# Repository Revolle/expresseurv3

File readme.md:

#Expresseur project

documentation , presentation : www.expresseur.com

basslua This library can be used by a GUI, to manage MIDI inputs and LUA scripting (to invent your own MIDI logic). C library 64 bits. Started by the GUI, which load :

main lua script to catch the midi-event
luachord.lua
luascore.lua
luabass
dependencies :

lua5.3 64 bits : www.lua.org
bass 64 bits : www.un4see.com
winmm/pc, coremidi/Mac
luabass :

This library can be used to manage audio output (MIDI, VST, SF2, wav, DMX) from a LUA script. C library 64 bits. Started by lua script, to render midi-out, SF2, VSTi, Wav

dependencies :

lua5.3 64 bits : www.lua.org
bass, bassmix, bassmidi ( bassasio/PC ) 64 bits: www.un4seen.com
winmm/pc, coremidi/Mac
vsti sdk (include only, dynamic VSTi-dll loaded dynamically on demand)
expresscmd :

This command-line can be used to launch basslua and luabass, and to interact with the LUA script. C exe command-line 64 bits. Starts basslua

dependencies :

basslua 64 bits
expresseur

This graphical User Interfacepresents two ways to play : improvisation and score-playing. C++ wxwidgets Graphic User Iinterface 64 bits. Starts basslua

dependencies

wxwidgets3.1 64 bits
basslua 64 bits
lilypond for the score rendering
mac

build wxwidgets 64 bits ( used by expresseur GUI ) :

cd Documents
git clone --recurse-submodules https://github.com/wxWidgets/wxWidgets.git
cd wxWidgets
mkdir build64
cd build64
../configure --with-macosx-version-min=10.15 --disable-shared --disable-sys-libs --prefix="$(pwd)"
make

build lua5.3.3 64 bits ( used by basslua & luabass )

cd $root_dir/../mac ( $root_dir is the platform where the git project is downloaded )
curl -O http://www.lua.org/ftp/lua-5.3.3.tar.gz
tar xf lua-5.3.3.tar.gz
rm lua-5.3.3.tar.gz
modification de src/Makefile : ligne macosx:
(
M
A
K
E
)
(ALL) SYSCFLAGS="-DLUA_USE_MACOSX -mmacosx-version-min=10.9 " SYSLIBS="-lreadline" CC=cc
make macosx
rtmidi : https://github.com/thestk/rtmidi.git

sound & Midi 64 bits libraries from www.un4seen.org : bass , bassmix, bassmidi

GNUmakefile builds the app package, with include & directories in mac directory

make -f GNUmakefile copy Expresseur.app ni Applications folder within Expresseur.app/Contents/MacOS : command-line "expresscmd" is available
pc

status : Solution 64 bits solution with Visual Studio available and operationnal. GNU Makefile not available.

Linux Ubuntu / Debian

build wxwidgets 64 bits ( used by expresseur GUI ) :

sudo apt-get install gtk2.0
git clone --recurse-submodules https://github.com/wxWidgets/wxWidgets.git
cd wxwidgets
mkdir buildgtk
cd buildgtk
../configure --with-gtk
make
sudo make install
sudo ldconfig
build lua 64 bits ( used by expresseur GUI ) :

sudo apt-get install libreadline6 libreadline6-dev
ou debian : sudo apt-get install libreadline7 libreadline-dev
cd linux/lua-5.3.4
make linux alsa dev package
sudo apt-get install libasound2-dev
rtmidi under linux/rtmidi from : https://github.com/thestk/rtmidi.git

sound/midi 64 bits lib under linux/bass .h and .so , from www.un4seen.org : bass , bassmix, bassmidi

GNUmakefile builds the epresseur package

make -f GNUmakefile cd expresseur/Expresseur.app/Contents/Linux :
./expresseur for the GUI,
or ./expresscmd for the command-line
to create a Gnome icone : adapt path in expresseurv3.desktop and copy to /usr/share/applications

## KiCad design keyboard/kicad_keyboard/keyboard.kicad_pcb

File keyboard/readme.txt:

Small keyboard with 3 keys and one button to play score on Expresseur.
It contains the 3D printing model, the Teensy-Arduino C code, the electronic wiring.

keyboard.scad 
Source code to describe the 3D model of the box. Use openScad freeware to export the three STL needed: keyboard_down , keyboard_up,  keybard_touch 

keyboard.ino
Teensy-Arduino C code , for Teensy-4 micro-controler

electronic-wiring

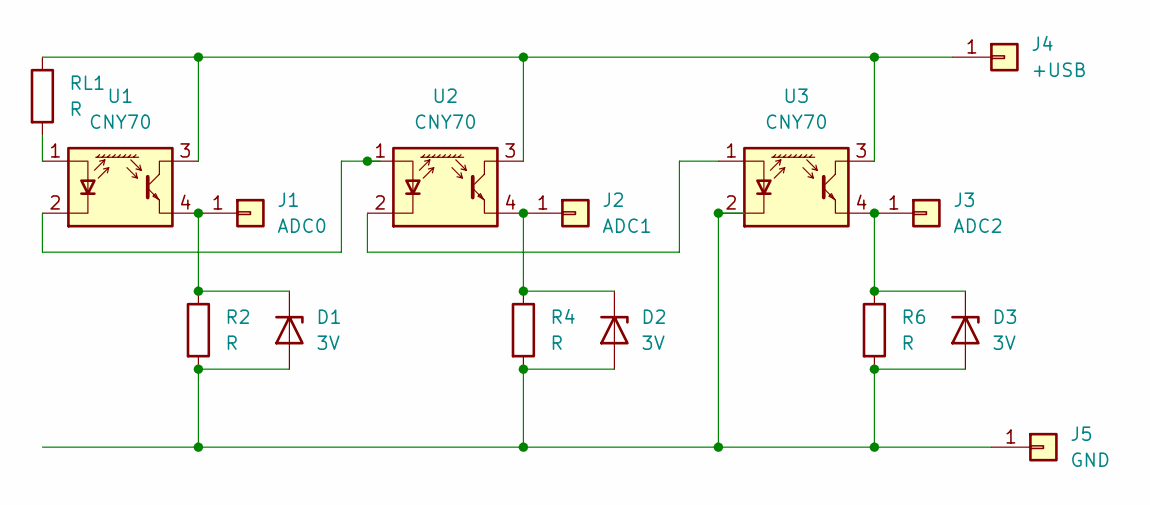
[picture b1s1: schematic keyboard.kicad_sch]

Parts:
D1, D2, D3: 3V; D_DO-35_SOD27_P7.62mm_Horizontal
J1: ADC0; SolderWire-0.15sqmm_1x01_D0.5mm_OD1.5mm
J2: ADC1; SolderWire-0.15sqmm_1x01_D0.5mm_OD1.5mm
J3: ADC2; SolderWire-0.15sqmm_1x01_D0.5mm_OD1.5mm
J4: +USB; SolderWire-0.15sqmm_1x01_D0.5mm_OD1.5mm
J5: GND; SolderWire-0.15sqmm_1x01_D0.5mm_OD1.5mm
R2, R4, R6: R; R_Axial_DIN0207_L6.3mm_D2.5mm_P7.62mm_Horizontal
RL1: R; R_Axial_DIN0207_L6.3mm_D2.5mm_P7.62mm_Horizontal
U1, U2, U3: CNY70; Vishay_CNY70

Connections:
unnamed: D1.2 (A), D2.2 (A), D3.2 (A), J5.1 (Pin_1_1), R2.2, R4.2, R6.2, U3.2 (K)
unnamed: D1.1 (K), J1.1 (Pin_1_1), R2.1, U1.4 (E)
unnamed: D2.1 (K), J2.1 (Pin_1_1), R4.1, U2.4 (E)
unnamed: D3.1 (K), J3.1 (Pin_1_1), R6.1, U3.4 (E)
unnamed: J4.1 (Pin_1_1), RL1.1, U1.3 (C), U2.3 (C), U3.3 (C)
unnamed: RL1.2, U1.1 (A)
unnamed: U1.2 (K), U2.1 (A)
unnamed: U2.2 (K), U3.1 (A)

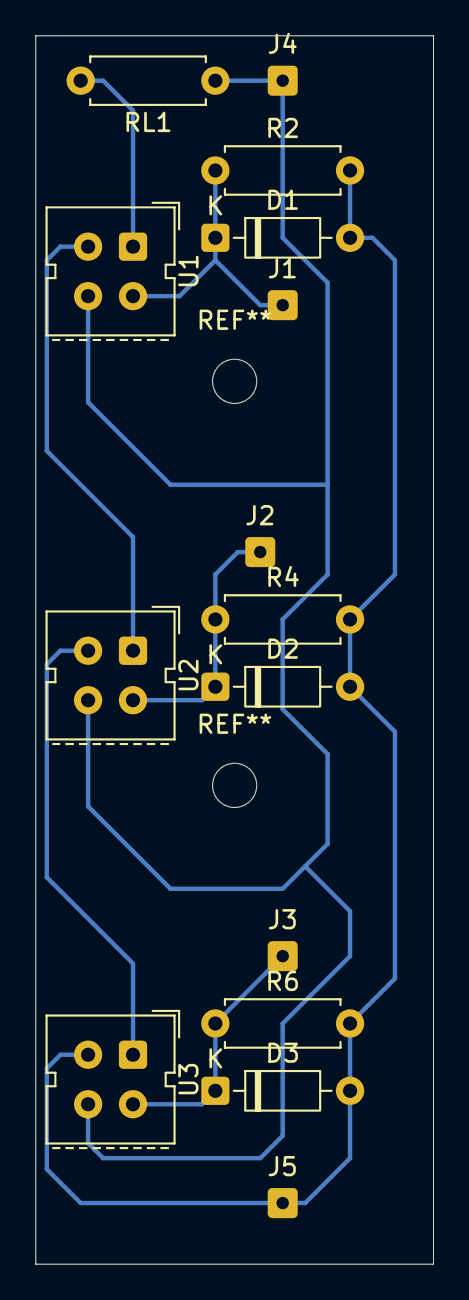
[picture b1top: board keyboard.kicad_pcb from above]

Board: 2 copper layers, 22.5 x 69.5 mm, 15 parts (0 on the bottom side), 8 nets.

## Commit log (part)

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2018-11-07 bak suppressed
2018-11-08 version 3.20 compilee sous Linux
2018-11-09 v3.2 in progress
2018-11-13 v3.2 windows beta
    v3.2 windows beta en cours de travail
2018-11-14 V3 beta progress
    V3 beta progress
2018-11-14 change presets
2018-11-14 type_msg in LUA parameter
    type_msg is passed to LUA when a selector is triggered
2018-11-20 tmp dir cleaner
2018-11-20 mlog empty
2018-11-21 direxists pour tmdir
2018-11-26 revision idel/paint
2018-11-27 test wxwidgets module
2018-11-27 revision idle paint in progress
2018-11-28 new display windows ok
2018-11-28 amelioration dc chords
2018-11-29 mod e viewer chord amélioré
2018-11-29 maj example rect chord
2018-11-29 info about cache score
2018-11-29 debug cache osx
2018-11-29 defaut shortcut
2018-11-30 compte refresh
2018-11-30 bug beats + nuances
    bug changement de mesure non recopié
    nuances lues dans le fichier xml
2018-11-30 control display result
2018-11-30 pg reset score mac
2018-11-30 onPaint true
2018-12-02 race MIDI
2018-12-02 debug note-thru
2018-12-02 note croix silencieuse
2018-12-03 optimisation refresh
2018-12-04 optimisation refresh screen bitmap
2018-12-06 test event-off=nil luascore
2018-12-11 temp files in user direcory
2018-12-11 debug temp files wnidows
2018-12-13 debug init
2018-12-13 workaround wxframe.setsize Mac
2018-12-14 shortcuts
2018-12-18 preset shortcut MIDI
2018-12-18 init avec prestes
2018-12-19 pianoSF2 en sf2
2018-12-19 defaultpianosf2
2018-12-19 supression preconfig LUA (jamais teste et trop complique)...
2018-12-21 debug expresscmd
2018-12-27 try-lock timer luabass basslua
2018-12-27 expresscmd bass play chord
2018-12-27 luabass outchordon delay error
2018-12-28 trylock external timer
2018-12-28 mutex_out + messagebox presets
2018-12-28 EndModal midishortcut
2018-12-28 test endmodal
2018-12-28 -maximize
2019-01-02 len control postlua
2019-01-04 color + end_score
2019-01-04 force install demo ressources
2019-01-04 dont recopy sf2 on start
2019-01-04 bug count ornaments
2019-01-07 supress test
2019-01-07 set style text read/write
2019-01-21 lua orament before / expresscmd.lua improved
2019-01-24 score background white
2019-01-24 debian
2019-01-25 gnome desktop
2019-01-25 gnome icone
2019-01-25 gnome icone 2
2019-01-25 clear turn page
2019-01-27 audio windows
2019-02-03 tuning chord mode
2019-02-04 comment in expresseur.lua
2019-02-15 legato=1 by default luachord.lua
2019-03-07 log midi and impro
2019-03-08 impro recording
2019-03-10 record impro
2019-03-10 lua actions simplified
2019-03-11 extended channel option
2019-09-17 clavier optique
    clavier optique
2019-10-04 ckavier optique
2019-10-04 fido keyboard
2019-10-04 fido keyb2
2019-10-10 lattitude dell
2019-10-16 pcb clavier
2019-10-17 pcb continuation
2019-10-18 pcb commande
2019-10-22 code teensy keyboard optic
2019-10-23 debugging code teensy keyboard
2019-10-24 analog swith on/off keyboard
2019-10-25 nettoyage claviers
2019-10-25 netoyage bis clavier
2019-11-03 trou jack usb boitier
2019-11-04 grosses pastilles
2019-11-05 grosse pastille
2019-11-12 legato score play
2019-11-12 legato sans comment
2019-11-13 hauterur boitier pour commande
2019-11-15 pcb keyboard
2019-11-24 legato score
2019-12-06 guitare
2020-01-24 raccourci clavier
2020-01-29 keydown
2020-01-30 module user
2020-01-31 debug luauser
2020-01-31 restrctioct copie luauser.lua
2020-01-31 debug onkeydown
2020-02-01 bug divisions variable
2020-02-01 optimisation lua retour
2020-02-02 luauser script as parameter
2020-02-02 simplification presets
2020-02-03 debug luauser.lua
2020-02-05 luauser improvment
2020-02-06 debug linux
2020-02-09 not reset on zero actio shortcut edit
2020-02-10 debug merge
2020-02-13 redistribution lua scripts
2020-02-13 redistribution lua scripts 2
2020-02-13 Update basslua.cpp
    debug lua merge
2020-02-14 debug filterevent
2020-02-14 divisions alignement
2020-02-14 suppression divisiosn description
2020-02-15 debug divisions
2020-02-16 keyboards
2020-02-17 keyboard disposal
2020-02-17 claviers
2020-02-17 debuk keyboard
    debug keyboard
2020-02-20 debug setup
2020-02-20 transpose inverse
2020-02-21 musescore v3
2020-02-23 musescore 3
2020-02-26 debug luachord
2020-02-26 program to lua
2020-03-01 debugluachord
2020-03-02 pad grand chose
2020-03-03 legato
2020-03-03 select gamme
2020-03-06 presets
2020-03-06 preset compliance
2020-03-06 bug control midi setting
2020-03-08 position chord
2020-03-08 debug position
2020-03-10 log position impro
2020-03-11 3.30
2020-03-12 azerty mac
2020-04-05 debig
2020-11-23 orgue
    ino pour l'orgue
2020-11-24 Update orgue.ino
    correction mineure
2020-11-26 debug orgue
    debug orgue
2020-12-05 debug orgue
2020-12-07 mélioration orgue
2020-12-30 organ debug
    AN
2020-12-30 paufinage orgue
2021-01-12 bug MIDI & Bug compile
2021-01-15 v3.3.1
2021-01-15 debug Mac
2021-01-22 V3.3.2
    RTMidi 4
2021-01-22 V3.4.0
    rtmidi.c/h directly included in the luabass project
2021-01-24 Mac V3.4.0 ok
2021-01-25 3.4.2
2021-02-10 pb path musescore mac
2021-02-28 rebug noteon noteoff orgue
2021-03-01 balance expresseur gauche droite
2021-03-08 simplification midiin midiout config
2021-03-08 bug nrdevice editshortcut
2021-03-08 bug selecteur
2021-03-10 bug selector ALT_x
2021-03-11 bug reset shortcut
2021-10-31 pa grand cgose
2022-02-18 config keydown
    change config of keydown
2022-02-18 cosmetique choix setting save
2022-02-19 struct setting files
2022-02-19 unused vars
2022-02-22 change one-key disposal
2022-03-04 reglage mixer clavier dans Expression
2022-03-24 bug impro
2022-03-24 black scale
    Prametre pour igorer les touches noires dans la scale impro
2023-05-11 Edit instruments on MIDI
2023-10-04 arpeggiate
    arpeggiate
    Visual Studio upgrade (recompile complete de wxwidgets et rtmidi)
2023-11-15 clavier v3
2023-11-18 clavier V3 bis
2023-11-18 ignore stl
2023-11-18 clean code
2023-11-20 3.3V max and OUTPUT_OPENDRAIN for LED output
2023-11-21 ledShow and Debug-print
2023-11-23 optimisation timers
2023-11-28 potar as mixer
    potar are used for MIDI CC if button pressed
    optical button pitch is shifted by buttons
2023-11-28 average on potar
    set adc with average for potars (static value)
    and no average for optical (slope measurement)
2023-12-04 individualisation des min max optical
2023-12-06 debug teensy4
    test ok : led potar button
    ledOnBoard
2023-12-08 antiparasitage optical button
2023-12-08 cosmetic
2023-12-10 ok version 0.1
2023-12-14 test unitaire ok
2023-12-15 clavier avec regression
    calcul de la velocité avec une regression pendant l'etat zombie du trigger
2023-12-16 finition
2024-01-04 luachord update
2024-01-05 first bass
    suppress fith bass on repeated chrd
2024-01-05 getAudioList bug
2024-02-05 potar button keyboard_v3.ino
2024-02-07 remove potar, upgrade button volume
2024-02-25 keyboard a 4 boutons
2024-02-26 Update keyboard_v3.ino
    Add Vmin config
2024-02-27 Update keyboard_v3.ino
    Led mangmt
2024-03-05 Update keyboard_v3.ino
    debug
2024-03-06 Update keyboard_v3.ino
    velocity curve
2024-03-08 USB-MIDI for control-change of Velocurve and veloMini
2024-04-24 compile
2024-05-16 https
2024-05-22 Lua volume
2024-06-17 luascore : lua commands
2024-11-24 CWD et modes
    Current xorking dirctory comme variable de reglage
    Mode mieux interprété
2025-04-27 upgrade wxwidget
2025-05-16 dmx and lilypond
2025-05-26 implemeattion
2025-06-06 devlelop continuation lilypond
2025-06-14 debut sebug lilypond expresseur
2025-06-15 lilypond command OK
2025-06-15 pos en cours de calcl
2025-06-17 generation et lecture lilypond OK
2025-06-17 all files expresseur OK
2025-06-18 debut affichage de partition
2025-06-18 affiche deux pages, fichier pos semble OK
2025-06-23 partions semble OK
2025-06-23 doc expresseur.lua
2025-06-24 paint managment and dmximprove
2025-06-24 appogiture ok
2025-06-24 test lilypod et dmx ok
2025-06-24 correction hampes
2025-06-25 ramping dmx
2025-06-25 netoyage bimap viewer onpaint
2025-06-26 triolets xml ok
2025-06-26 cross note
2025-06-27 destructeurs musicxml
2025-06-27 bug jardinage
    vesion debug OK
    versoin non-debuk : jardinage
2025-07-19 debug memory leaks
    Comment a lot in expresseur.cpp
2025-07-20 config en C static
    pas de fuite
2025-07-22 rajout de luafile
    pas de memory leak
2025-07-23 suppression _string
    zero memory leak
2025-08-17 std::vector
    Remplacement WXLIST par std::vector
2025-08-22 compil ok
    no more memory leak
    lilypond to be tested
2025-08-23 lilypond affiche
    pas de fuite memoire
    lilypond process et affichage ok
    pb : rythme expresseur KO
2025-08-23 rafraichissement score
    renovation rafraichissement score
2025-08-23 clarefontaine bien affichee
2025-08-25 move pointer to static
    compile OK
    Load XML bizarre
2025-08-26 gestion xml OK
    Il sembe que la structre score est bien remplie.
    PB sur les calsuls dans la compilation ? (durée de note, ... )
2025-08-26 debut daffichage de la partition
    Bug sur la partie Expresseur
2025-08-27 Partition expresseur OK
2025-08-27 suppression classe c_default_xy
    suppression classe c_default_xy
2025-08-28 natureboy OK
    suppression "sounds" en sortie
2025-08-28 comportement global OK
2025-08-29 pb words et maximize
    init segno coda musicxml.
    Gestion etat mximized
2025-08-29 arpegiate OK
2025-08-29 release OK
2025-08-30 macos catalina
2025-08-30 Update readme.md Mac
2025-09-01 init config dynamique
2025-09-01 compilMac
2025-09-03 affichage ok macosx
2025-09-03 lily 2.28 PC
    Ne march epas : 2.28 lilypon en panne
2025-09-04 dmx change
    library serialport
    hook noteon => dmx
2025-09-05 wizard DMX
    debut
2025-09-05 debug wizard dmx
    pb setsizer dmx wizard
2025-09-07 setting test DMX OK
2025-09-08 compil mac serialdmx lib
2025-09-21 navigation accord improvisee
2025-09-30 lilypond2.25.29
2025-10-01 erreur load luabass
2025-10-02 windows 3.55 setup ok
2025-10-02 dmx track offset 1
2025-10-04 dedoublement paroles
2025-10-05 contournement bug musicxml2py hyphen
2025-10-17 version macmini presque ok
2025-10-23 arpege pb pointeur resolu
2025-10-23 Check update
    Fonctionne que dans le GUI. Pas dans le destructeur de la classe Expresseur
2025-10-30 resource files
2025-10-30 make clean, make all
2025-10-30 claire fntaie tenor
2025-10-30 Fine OK
2025-11-19 Refactor optical button logic and parameters
    Updated optical button handling and parameters for MIDI keyboard.
2025-11-19 Refactor comments and variable names in keyboard_v3.ino
    Updated comments for clarity on MIDI keyboard functionality and improved variable naming for onboard LED.
2025-11-20 compile arduino keyboard ok
2025-11-20 debuggage grace note
2025-11-20 grace debugge
2025-11-28 log open midi
2025-11-30 pedalier update
2025-12-01 Refactor MIDI keyboard and tuning logic
    Updated MIDI keyboard functionality and tuning parameters.
2025-12-01 Add MIDI channel and output functions
    Added functions to set MIDI channel and output number, and included note on functionality.
2025-12-01 Implement splash screen for music score processing
    Added splash screen functionality for processing.
2025-12-01 lilypond splash screen
2025-12-04 lilypons 2.25.30
2025-12-04 mixer debug
2025-12-04 lilypond gnu
2025-12-15 Implement error handling for ADC reads
    Added error handling for ADC single read operations in opticalAdcPreset function.
2025-12-16 Refactor EEPROM functions and add tuning logic
    Refactor EEPROM read/write functions to accept a boolean parameter for additional functionality. Introduce tuning logic on startup and adjust optical button structure.
2025-12-16 Refactor EEPROM handling and optical button logic
2025-12-16 Refactor pedalier.scad for improved structure
2025-12-17 Refactor ledOnboardFlash function and its calls
2025-12-18 keyboard OK
    Avec bouton reset config
2025-12-18 Update keyboard_v3.ino
    midi CC OK
2025-12-18 Update keyboard_v3.ino
    CC midi ok
2025-12-19 Update keyboard_v3.ino
    pas d'exclusion noteon
2025-12-19 no overlap score
2025-12-26 wrapline lilypond
    lines are wrapped in lilypon score, readjust calculation of posnote according tie the antislash (start of the note ?)
2026-01-12 Implement Control Change for optical buttons CC104 and CC105
    Added Control Change handling for optical buttons.
